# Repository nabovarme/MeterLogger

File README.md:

# MeterLogger

MeterLogger is a custom daughterboard you can insert in Kamstrup Meters and get them to transmit their samples 
to a remote MQTT server.
MeterLogger is part of the [**Nabovarme**](https://github.com/nabovarme) organization.

Check out the [WIKI](https://github.com/nabovarme/MeterLogger/wiki) for more details!

## 🚀 Modern GUI-Based Flashing & Rebuilding

You no longer need local compilers, toolchains, or command-line flash utilities on your host machine. Building and flashing are now fully virtualized via Docker and executed directly from your web browser.

### How to Flash:
1. Navigate to the **Firmware Flash Tool** tab on your MeterLoggerWeb dashboard
2. Connect your ESP8266/MeterLogger board via USB.
3. Select your desired firmware profile from the search bar (tied directly to your meter serial).
4. Click **Flash Device**. Your browser will request access to the USB serial port via the **WebSerial API** and write the firmware directly at up to 1.5 Mbps.

### How to Rebuild Custom Firmware:
If you need custom parameters (e.g., turning an EN61107 meter into an Impulse meter or disabling Auto-Close):
1. Expand the **Custom Firmware Build Settings** panel.
2. Select your targets (e.g., Protocol, Valve overrides, debug flags).
3. Click **Rebuild Firmware**.
4. This dispatches an asynchronous build task to the Dockerized `firmware_builder` service on your host. Once compiled (usually < 30 seconds), the new image is indexed and immediately ready to be flashed in the selector above.

## Build details (old procedure)

To build and flash for KMP type meter (Multical 601):  
```
KEY=ef500c9268cf749016d26d6cbfaaf7bf make clean all flashall
```
 
To build and flash for EN61107, sub type Multical 66 C:  
```
EN61107=1 KEY=ef500c9268cf749016d26d6cbfaaf7bf make clean all flashall
```
 
To build and flash for EN61107, sub type Multical 66 B:  
```
MC_66B=1 KEY=ef500c9268cf749016d26d6cbfaaf7bf make clean all flashall
```
 
To build and flash for KMP/EN61107 type, forced as flow meter:  
```
FLOW_METER=1 KEY=ef500c9268cf749016d26d6cbfaaf7bf make clean all flashall
```
 
To build and flash for impulse-based electricity meter:  
```
IMPULSE=1 KEY=ef500c9268cf749016d26d6cbfaaf7bf make clean all flashall
```
 
To configure wireless network:  
```
SERIAL=9999999 KEY=ef500c9268cf749016d26d6cbfaaf7bf make wifisetup
```
 
**BUILD OPTIONS**  

DEBUG=1  
enable serial debugging  

DEBUG_NO_METER=1  
don't wait for meter to answer serial. Build for nodemcu board  

IMPULSE_DEV_BOARD=1  
build for nodemcu board  

DEBUG_SHORT_WEB_CONFIG_TIME=1  
don't wait for web config  

IMPULSE=1  
meter type is impulse-based (100 mS)  

EN61107=0  
meter type is KMP (Multical 601)  

EN61107=1  
meter type is EN61107, sub type Multical 66 C  

MC_66B=1  
meter type is EN61107, sub type Multical 66 B  

FLOW_METER=1  
meter is forced to run as a flow meter and close when volume is reached  

AUTO_CLOSE=1  
automatically check if energy is larger than the value set by open_until MQTT command  

DEBUG_STACK_TRACE=1  
Enable exception stack trace dump to flash at address STACK_TRACE_SEC * SPI_FLASH_SEC_SIZE (0x80000), STACK_TRACE_N bytes  

DISABLE_LED=1  
completely disable LED blinking routines and hardware setup while keeping API stub functions intact  

NO_CRON=1  
disable cron stuff and save 2688 bytes of RAM. Reconfiguration is needed after changing this  

THERMO_NO=0  
thermo actuator is normally closed  

THERMO_NO=1  
thermo actuator is normally open  

THERMO_ON_AC_2  
thermo actuator connected on AC 2  

LED_ON_AC=1  
use LED to indicate AC state  

AC_TEST=1  
run a test pattern on AC out and blink LED  

SERIAL=9999999  
serial number for meter used for device's SSID: IMPULSE meters EL_9999999 and other Kamstrup meters KAM_9999999. Used in make wifisetup target and if DEBUG_NO_METER=1  

KEY=ef500c9268cf749016d26d6cbfaaf7bf  
master key for crypto, 16 bytes  
First 8 bytes hex encoded (ef500c9268cf7490) is Wi-Fi setup password. Master key is SHA256 hashed to 32 bytes and first 16 bytes is AES key and last 16 bytes is HMAC SHA256 key.

```
master key                            wifi key (first 16 bytes)
+--------------------------------+    +----------------+
|ef500c9268cf749016d26d6cbfaaf7bf| -> |ef500c9268cf7490| 
+--------------------------------+    +----------------+
                |
          [sha256 hash]
                |
                v
+----------------------------------------------------------------+
|89a5d4f82ad86bc9ec27427e246fd15481663afea8c463d93cc93c967c9b31be|
+----------------------------------------------------------------+
                |                                        |
aes key         v                   hmac sha256 key      v
+--------------------------------+  +--------------------------------+
|89a5d4f82ad86bc9ec27427e246fd154|  |81663afea8c463d93cc93c967c9b31be|
+--------------------------------+  +--------------------------------+

```

Crypto is applied on MQTT packages like this:
1) at 32 bytes offset in mqtt_message contains IV, 16 bytes random bytes used for AES128 CBC encryption.

2) cleartext (0-terminated) is AES128 CBC encrypted, with AES key and IV. Result is written to mqtt_message at 32 + 16 bytes offset (binary data not 0-terminated).

3) HMAC SHA256 checksum is calculated on topic + IV + encrypted data and written to first 32 bytes.

```
hmac sha256                                                       IV                               encrypted data
+----------------------------------------------------------------+--------------------------------+------------------------------------+
|b218d7ec2f7977c942b5bf16d535de3cb5f0e012638148e5a7fc6e09efe440a7|54cd3d04f024e7e5c4876248cc146c41|9616bb291182861b7a5ea238a0c267115...|
+--------------------------------------------------------------------------------------------------------------------------------------+

IV
+--------------------------------+
|54cd3d04f024e7e5c4876248cc146c41| 
+--------------------------------+

cleartext message (null terminated)
+-----------------------------------------------------------------------------------------------------------------+
|heap=21376&t1=23.61 C&t2=22.19 C&tdif=1.42 K&flow1=0 l/h&effect1=0.0 kW&hr=73327 h&v1=1321.27 m3&e1=56.726 MWh&\0|
+-----------------------------------------------------------------------------------------------------------------+

+

hmac sha256 key
```

## Flash Memory Map (1MB ESP07)

The firmware relies on a strict dual-ROM partition layout to support rBoot Over-The-Air (OTA) updates and a dedicated LittleFS/ESPFS webserver filesystem. It is critical that configuration blocks and crash logs do not overlap with executable ROM spaces.

| Start Address | End Address | Size (KB) | Purpose |
| :--- | :--- | :--- | :--- |
| `0x00000` | `0x00FFF` | 4 KB | **rBoot Bootloader** (`rboot.bin`) |
| `0x01000` | `0x01FFF` | 4 KB | **rBoot Configuration** (`blank.bin`) |
| `0x02000` | `0x75FFF` | 464 KB | **ROM 0** (`user1.bin` / Primary Firmware Slot) |
| `0x76000` | `0x7BFFF` | 24 KB | **System Configuration** (`CFG_LOCATION` / Wi-Fi credentials & states) |
| `0x7C000` | `0x81FFF` | 24 KB | **Web UI Filesystem** (`webpages.espfs` / HTML/CSS/JS assets) |
| `0x82000` | `0xF7FFF` | 472 KB | **ROM 1** (`user2.bin` / Secondary OTA Firmware Slot) |
| `0xF8000` | `0xFBFFF` | 16 KB | **Stack Trace Crash Log** (`STACK_TRACE_SEC` / Exception Handler dumps) |
| `0xFC000` | `0xFDFFF` | 8 KB | **ESP8266 System Init Data** (`esp_init_data_default_112th_byte_0x03.bin`) |
| `0xFE000` | `0xFFFFF` | 8 KB | **System Blank** (`blank.bin`) |

*Note: The `STACK_TRACE_SEC` must be strictly set to `0xF8` in `user_config.h` to prevent the crash logger from corrupting ROM 1 or the web filesystem during exception handling.*

**MQTT format for messages sent _to_ meter**  

| Topic                                               | Message                                                                                                                                            |
| :-------------------------------------------------- | :------------------------------------------------------------------------------------------------------------------------------------------------- |
| /config/v2/9999999/[unix time]/open_until           | [kWh when meter should close (only write to flash if changed and not negative value)]                                                              |
| /config/v2/9999999/[unix time]/open_until_delta     | [[kWh when meter should close as delta (only write to flash if changed and not negative value)]                                                    |
| /config/v2/9999999/[unix time]/set_cron             | minute=30&hour=*&day_of_month=*&month=*&day_of_week=*&command=[open\|close\|set_ssid_pwd...\|clear_cron]                                           |
| /config/v2/9999999/[unix time]/read_stack_trace     | [offset=0] Requests a chunk of the saved exception handler crash log.                                                                              |
| /config/v2/9999999/[unix time]/set_ssid             | [ssid]                                                                                                                                             |
| /config/v2/9999999/[unix time]/set_pwd              | [pwd]                                                                                                                                              |
| /config/v2/9999999/[unix time]/set_ssid_pwd         | [ssid=name&pwd=secret]                                                                                                                             |
| /config/v2/9999999/[unix time]/test_ssid_pwd        | [ssid=name&pwd=secret&stay=seconds]                                                                                                                |
| /config/v2/9999999/[unix time]/set_ap_mesh_pwd      | [pwd]                                                                                                                                              |
| /config/v2/9999999/[unix time]/start_fallback_ap    | [seconds] temporarily broadcasts the fallback rescue network (no flash write)                                                                      |
| /config/v2/9999999/[unix time]/ota_update           | [url=http://domain.com/api&version=20261013_001000&sha256_user1=<64-char_hex_hash>&sha256_user2=<64-char_hex_hash>] (all optional; meter selects correct hash based on target slot) OR [action=confirm] (permanently commits) |
| /config/v2/9999999/[unix time]/set_key              | [key=new_32_char_hex_key]                                                                                                                          |
| /config/v2/9999999/[unix time]/set_mqtt_host        | [MQTT hostname, e.g. nabovarme.meterlogger.net; saved to flash and device restarts after replying]                                                 |
| &nbsp;                                              | &nbsp;                                                                                                                                             |
| /config/v2/9999999/[unix time]/ping                 |                                                                                                                                                    |
| /config/v2/9999999/[unix time]/open                 |                                                                                                                                                    |
| /config/v2/9999999/[unix time]/close                |                                                                                                                                                    |
| /config/v2/9999999/[unix time]/status               |                                                                                                                                                    |
| /config/v2/9999999/[unix time]/cron                 |                                                                                                                                                    |
| /config/v2/9999999/[unix time]/clear_cron           |                                                                                                                                                    |
| /config/v2/9999999/[unix time]/version              |                                                                                                                                                    |
| /config/v2/9999999/[unix time]/uptime               |                                                                                                                                                    |
| /config/v2/9999999/[unix time]/vdd                  |                                                                                                                                                    |
| /config/v2/9999999/[unix time]/rssi                 |                                                                                                                                                    |
| /config/v2/9999999/[unix time]/ssid                 |                                                                                                                                                    |
| /config/v2/9999999/[unix time]/scan                 |                                                                                                                                                    |
| /config/v2/9999999/[unix time]/wifi_status          |                                                                                                                                                    |
| /config/v2/9999999/[unix time]/start_ap             |                                                                                                                                                    |
| /config/v2/9999999/[unix time]/stop_ap              |                                                                                                                                                    |
| /config/v2/9999999/[unix time]/fallback_status      |                                                                                                                                                    |
| /config/v2/9999999/[unix time]/ap_status            |                                                                                                                                                    |
| /config/v2/9999999/[unix time]/reconnect            |                                                                                                                                                    |
| /config/v2/9999999/[unix time]/disconnect_count     |                                                                                                                                                    |
| /config/v2/9999999/[unix time]/network_quality      |                                                                                                                                                    |
| /config/v2/9999999/[unix time]/mem                  |                                                                                                                                                    |
| /config/v2/9999999/[unix time]/chip_id              |                                                                                                                                                    |
| /config/v2/9999999/[unix time]/flash_id             |                                                                                                                                                    |
| /config/v2/9999999/[unix time]/flash_size           |                                                                                                                                                    |
| /config/v2/9999999/[unix time]/crypto               |                                                                                                                                                    |
| /config/v2/9999999/[unix time]/reset_reason         |                                                                                                                                                    |
| /config/v2/9999999/[unix time]/restart              |                                                                                                                                                    |

**MQTT format for messages sent _from_ meter**  

| Topic | Message |
| :--- | :--- |
| /sample/v2/9999999/[unix time]                      | heap=20000&t1=25.00 C&t2=15.00 C&tdif=10.00 K&flow1=0 l/h&effect1=0.0 kW&hr=0 h&v1=0.00 m3&e1=0 kWh&                                               |
| /cron/v2/9999999/[unix time]                        | [number of active cron jobs]                                                                                                                       |
| /ping/v2/9999999/[unix time]                        |                                                                                                                                                    |
| /version/v2/9999999/[unix time]                     | [sdk version]-[git version]-[lwip version]-[hardware model]                                                                                        |
| /status/v2/9999999/[unix time]                      | [open\|close]                                                                                                                                      |
| /open_until/v2/9999999/[unix time]                  | [kWh when meter should close]                                                                                                                      |
| /open_until_delta/v2/9999999/[unix time]            | [kWh when meter should close]                                                                                                                      |
| /uptime/v2/9999999/[unix time]                      | [uptime in seconds]                                                                                                                                |
| /stack_trace_result/v2/9999999/[unix time]          | [offset=0&data=Stack%20dump%3A%0A...] URL-escaped block of the recorded stack trace. Returns empty data if end of log is reached.                  |
| /vdd/v2/9999999/[unix time]                         | [power supply voltage level]                                                                                                                       |
| /rssi/v2/9999999/[unix time]                        | [rssi of the wifi it is connected to (in dBm, 31 if fail)]                                                                                         |
| /ssid/v2/9999999/[unix time]                        | [ssid of the wifi it is connected to]                                                                                                              |
| /set_ssid/v2/9999999/[unix time]                    | [ssid of the wifi it is set to connect to]                                                                                                         |
| /set_pwd/v2/9999999/[unix time]                     | [password for the wifi it is set to connect to]                                                                                                    |
| /set_ssid_pwd/v2/9999999/[unix time]                | ssid=[name]&pwd=[secret]                                                                                                                           |
| /test_ssid_pwd/v2/9999999/[unix time]               | ssid=[name]&pwd=[secret]&stay=[seconds]                                                                                                            |
| /test_ssid_pwd_result/v2/9999999/[unix time]        | [status=ok&ssid=the_ssid&rssi=-62&reason=none&time_ms=3100] (or status=failed&ssid=the_ssid&rssi=0&reason=4way_handshake_timeout&time_ms=15000)    |
| /set_ap_mesh_pwd/v2/9999999/[unix time]             | [password for the mesh-[serial] itself]                                                                                                            |
| /scan/v2/9999999/[unix time]                        | [empty reply to acknowledge scan command]                                                                                                          |
| /scan_result/v2/9999999/[unix time]                 | [ssid=Loppen Public&bssid=xx:xx:xx:xx:xx:xx&rssi=-51&channel=11&auth_mode=...&pairwise_cipher=...&group_cipher=...&phy_11b=...&phy_11g=...&phy_11n=...&wps=...] |
| /start_fallback_ap/v2/9999999/[unix time]           | [seconds] immediate parameter echo                                                                                                                 |
| /fallback_status/v2/9999999/[unix time]             | [active\|inactive]                                                                                                                                 |
| /wifi_status/v2/9999999/[unix time]                 | [connected|<disconnect_reason_string>] (e.g., connected, no_ap_found, auth_expire)                                                                 |
| /ap_status/v2/9999999/[unix time]                   | [started\|stopped]                                                                                                                                 |
| /disconnect_count/v2/9999999/[unix time]            | [number of disconnects]                                                                                                                            |
| /network_quality/v2/9999999/[unix time]             | ping_response_time=[2.000 mS\|unknown]&ping_average_packet_loss=[0.00%\|unknown]&disconnect_count=[0]                                              |
| /cnx_csa_fn_called/v2/9999999/[unix time]           | count=[number of intercepted CSA calls]                                                                                                            |
| /flash_error/v2/9999999/[unix time]                 | calculated_crc=[0x...]&saved_crc=[0x...]                                                                                                           |
| /mem/v2/9999999/[unix time]                         | heap=9672                                                                                                                                          |
| /flash_id/v2/9999999/[unix time]                    | 0x164020                                                                                                                                           |
| /flash_size/v2/9999999/[unix time]                  | 4096 kB                                                                                                                                            |
| /reset_reason/v2/9999999/[unix time]                | reason=[int]&exccause=[int]&epc1=[0x...]&epc2=[0x...]&epc3=[0x...]&excvaddr=[0x...]&depc=[0x...]                                                   |
| /restart/v2/9999999/[unix time]                     |                                                                                                                                                    |
| /ota_update/v2/9999999/[unix time]                  | [status=started&target_rom=1\|2] (Progress: status=flashing_10%..90%. Success: status=success&target_rom=1\|2, status=restarting_in_22s, status=self_test_passed_committed, status=already_committed. Errors: status=error\_...) |
| /set_key/v2/9999999/[unix time]                     | [status=ok (or status=error_invalid_key)]                                                                                                          |
| /set_mqtt_host/v2/9999999/[unix time]               | [status=ok (or status=error_invalid_host)]                                                                                                         |

**Secure OTA Updates with Dual SHA-256 Validation:**  
The OTA (Over-The-Air) firmware update process now features streaming cryptographic verification to prevent corrupted downloads from soft-bricking the device. Because the ESP8266 rBoot bootloader requires two separate memory slots, user1.bin and user2.bin are compiled with different memory layouts and consequently have completely different SHA-256 hashes.

To ensure safety without requiring the server to track which slot the meter is currently using, the MQTT RPC payload accepts both hashes (sha256_user1 and sha256_user2). As the meter streams the HTTP download into flash, it calculates the SHA-256 hash on the fly. Before switching the boot slot, it verifies the downloaded file against both provided hashes. If the checksum does not match, the update is aborted, an error is reported over MQTT, and the device safely reboots into the existing valid firmware.

**Note on Wi-Fi Test Reason Codes:**  
The `reason` field in the `/test_ssid_pwd_result` payload maps to ESP8266 SDK disconnect codes. The most common are:
* **none**: Success (No error)
* **4way_handshake_timeout**: Wrong Password 
* **no_ap_found**: Network Not Found / Out of Range
* **auth_expire**: AP Rejected Authentication 
* **timeout**: Custom code for internal timeout (Test took longer than 15 seconds)

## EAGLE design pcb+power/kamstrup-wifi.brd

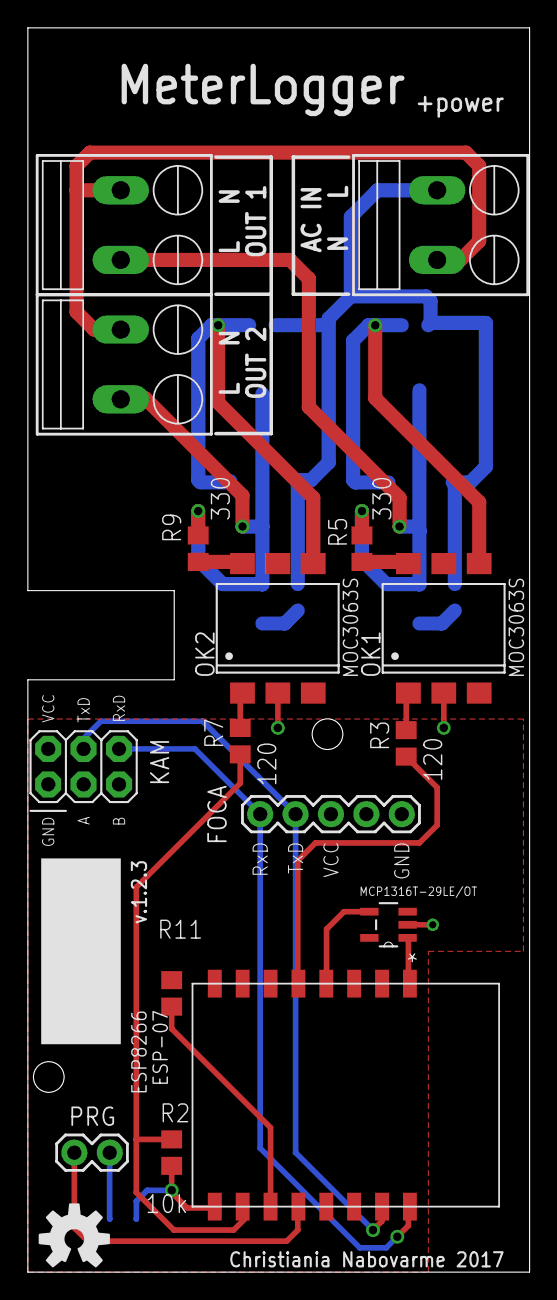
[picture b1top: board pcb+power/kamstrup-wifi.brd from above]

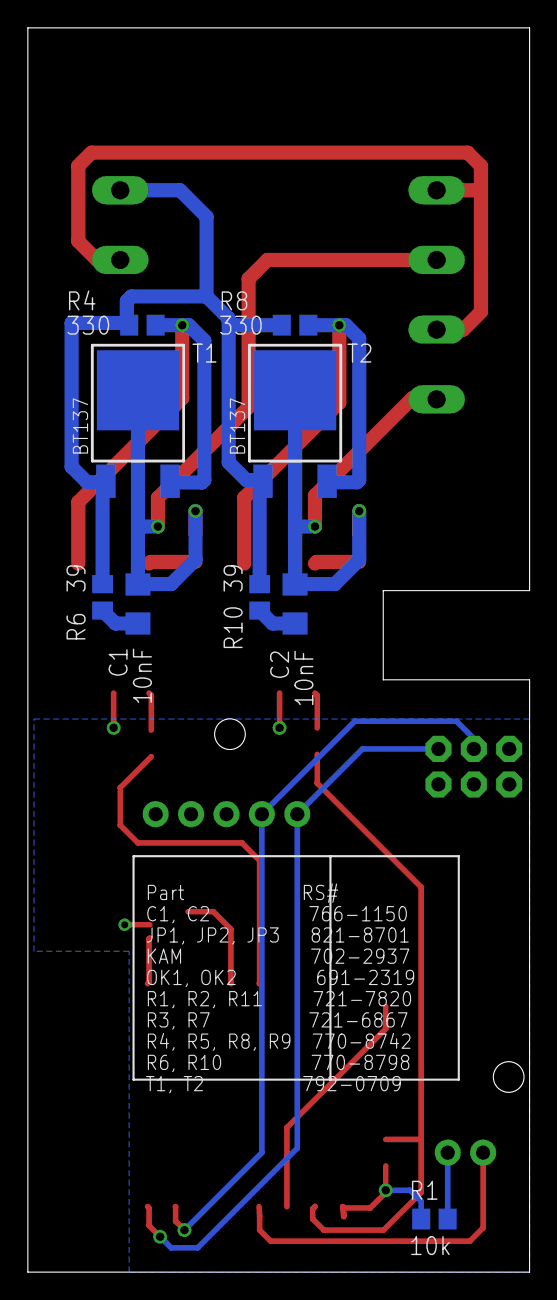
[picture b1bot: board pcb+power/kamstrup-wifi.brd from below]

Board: 2 copper layers, 36.0 x 89.3 mm, 26 parts (9 on the bottom side), 23 nets.

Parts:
C1, C2: 10nF; C1206
FOCA: 1X05
JP1: AC IN; SCREWTERMINAL-5MM-2
JP2: AC OUT 1; SCREWTERMINAL-5MM-2
JP3: AC OUT 2; SCREWTERMINAL-5MM-2
KAM: 2X03
OK1, OK2: MOC3063S; DIL6-SMD
PRG: M02PTH; 1X02
R1, R2, R11: 10k; R0805
R3, R7: 120; R0805
R4, R5, R8, R9: 330; R0805
R6, R10: 39; R0805
T1, T2: BT137; SOT428
U1: ESP8266-07; ESP-07
U2: MCP1316T-29LE/OT; SOT95P270X145-5N
U$2: OSHW-LOGO-M

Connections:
3.3V: FOCA.3, KAM.2, R11.1, U1.CH_PD, U1.VCC, U2.5
GND: FOCA.5, KAM.1, OK1.2, OK2.2, R1.1, R2.1, U1.GND, U2.2
unnamed: FOCA.1, KAM.6, U1.TXD
unnamed: FOCA.2, KAM.4, U1.RXD
unnamed: PRG.2, U1.GPIO0
unnamed: PRG.1, R1.2
unnamed: OK2.1, R7.2
unnamed: OK2.4, R8.1, T2.3
unnamed: OK2.6, R9.1
unnamed: C2.1, JP3.2, R9.2, T2.4
unnamed: JP1.1, R4.2, R6.1, R8.2, R10.1, T1.1, T2.1
unnamed: C2.2, R10.2
unnamed: R3.1, U1.GPIO14
unnamed: OK1.1, R3.2
unnamed: OK1.4, R4.1, T1.3
unnamed: OK1.6, R5.1
unnamed: C1.1, JP2.2, R5.2, T1.4
unnamed: R2.2, R7.1, U1.GPIO15
unnamed: C1.2, R6.2
unnamed: JP1.2, JP2.1, JP3.1
unnamed: U1.REST, U2.1
unnamed: U1.GPIO16, U2.4
unnamed: R11.2, U1.GPIO2

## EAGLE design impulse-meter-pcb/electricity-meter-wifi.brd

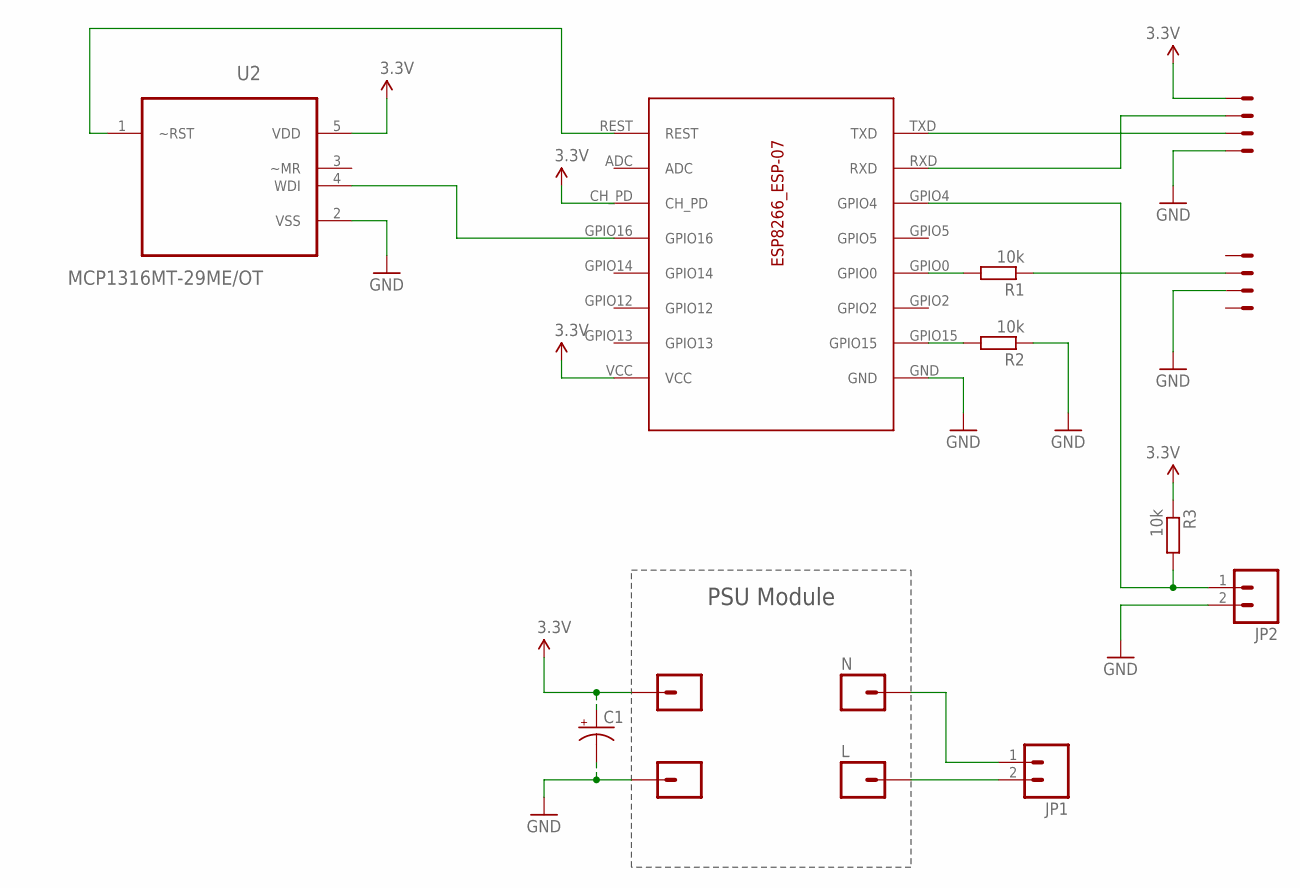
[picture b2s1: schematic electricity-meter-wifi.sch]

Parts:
3.3V: M01PTH_2MM; 1X01_2MM
C1: CAP_POLD; PANASONIC_D
ESP8266_ESP-07: ESP8266-07; ESP-07
GND: M01PTH_2MM; 1X01_2MM
JP1, JP2: M02PTH3_5MM; 1X02_LONGPADS
L: M01PTH_2MM; 1X01_2MM
N: M01PTH_2MM; 1X01_2MM
R1, R2, R3: 10k; R0805
U2: MCP1316MT-29ME/OT; SOT95P270X145-5N
U$1: CON-PCB-SLOT-0.05MINIMAL; CONN_SLOT_MINIMAL

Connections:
3.3V: 3.3V.1, C1.+, ESP8266_ESP-07.CH_PD, ESP8266_ESP-07.VCC, R3.1, U2.5 (VDD), U$1.4; also elsewhere on the board
GND: C1.-, ESP8266_ESP-07.GND, GND.1, JP2.2, R2.1, U2.2 (VSS), U$1.1, U$1.7; also elsewhere on the board
unnamed: ESP8266_ESP-07.TXD, U$1.2
unnamed: ESP8266_ESP-07.RXD, U$1.3
unnamed: ESP8266_ESP-07.GPIO4, JP2.1, R3.2
unnamed: ESP8266_ESP-07.GPIO0, R1.2
unnamed: JP1.2, L.1
unnamed: JP1.1, N.1
unnamed 8: ESP8266_ESP-07.GPIO15, R2.2; also elsewhere on the board
unnamed: ESP8266_ESP-07.REST, U2.1 (~RST)
unnamed: ESP8266_ESP-07.GPIO16, U2.4 (WDI)
unnamed 11: ESP8266_ESP-07.GPIO12; also elsewhere on the board
unnamed: R1.1, U$1.6
unnamed 13: ESP8266_ESP-07.GPIO13; also elsewhere on the board
unnamed 14: ESP8266_ESP-07.GPIO14; also elsewhere on the board
unnamed 15: ESP8266_ESP-07.GPIO2; also elsewhere on the board

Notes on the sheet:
PSU Module

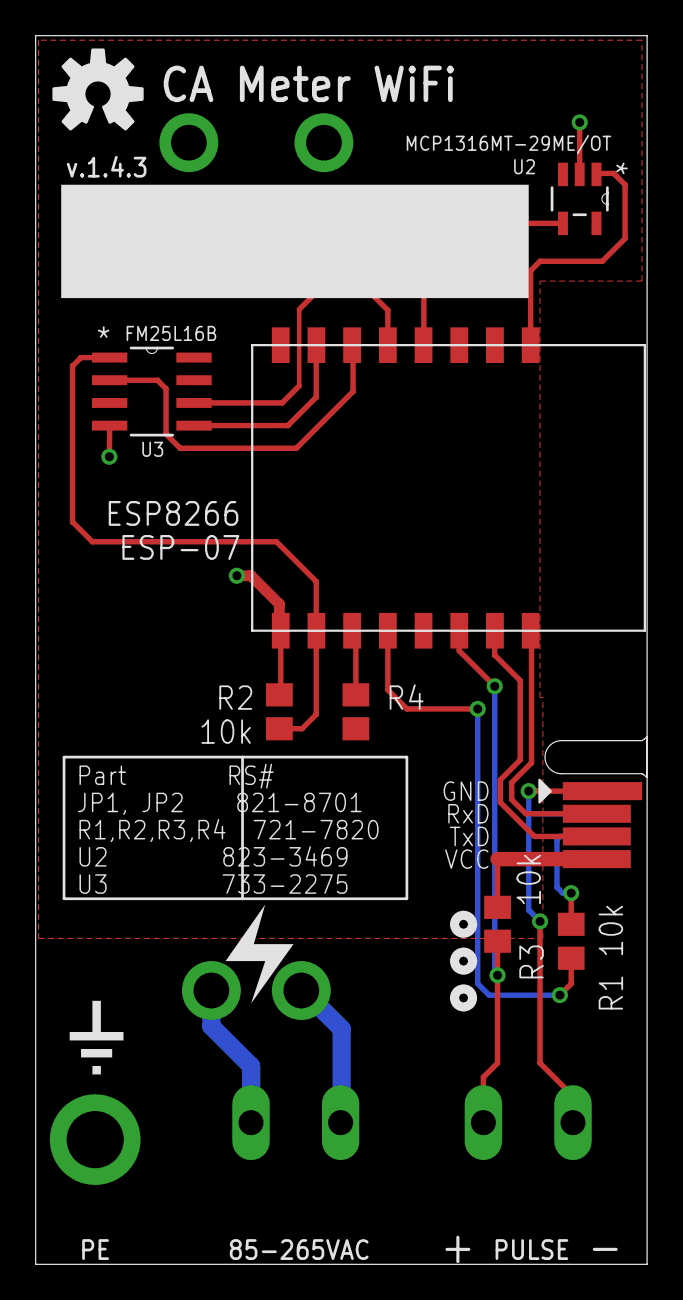
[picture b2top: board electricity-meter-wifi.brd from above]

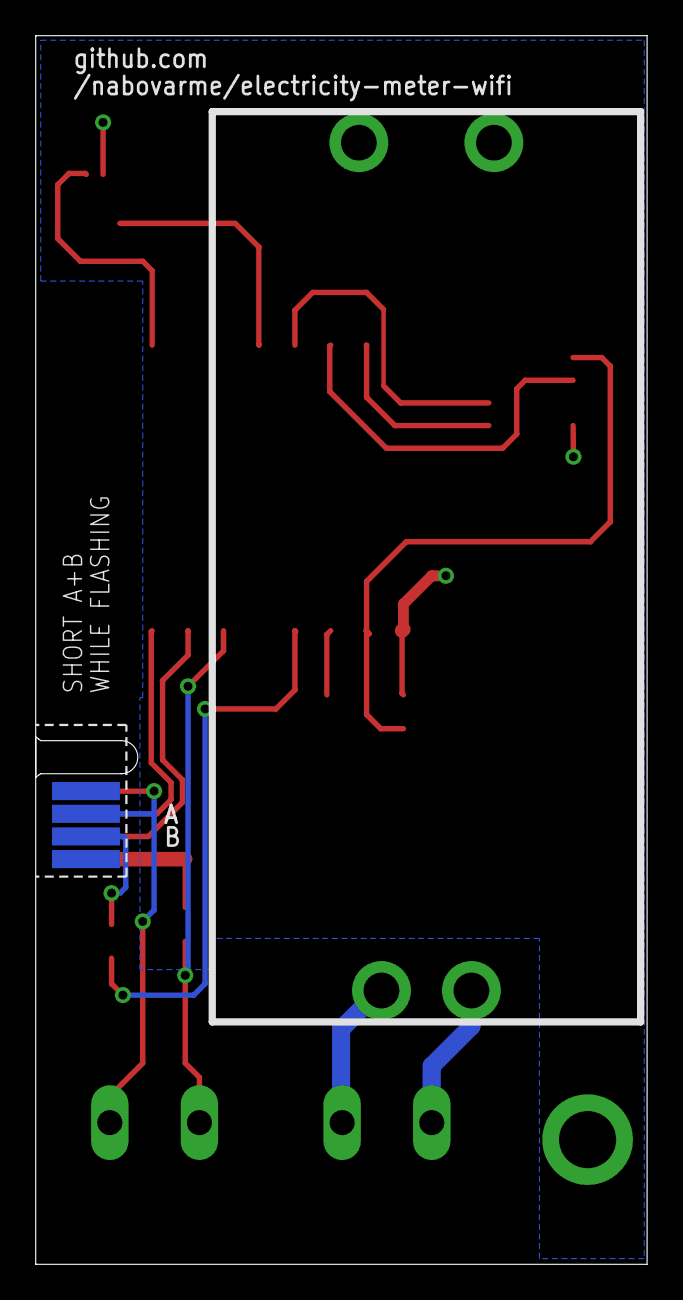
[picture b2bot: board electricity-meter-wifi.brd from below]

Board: 2 copper layers, 34.3 x 68.8 mm, 15 parts (4 on the bottom side), 16 nets.

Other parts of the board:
R4: 10k; R0805
U3: FM25L16B; SOIC127P600X175-8N
U$2: OSHW-LOGO-M

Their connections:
3.3V: R4.1, U3.3, U3.7, U3.8; also elsewhere on the board
GND: U3.4; also elsewhere on the board
unnamed 8: U3.1; also elsewhere on the board
unnamed 11: U3.2; also elsewhere on the board
unnamed 13: U3.5; also elsewhere on the board
unnamed 14: U3.6; also elsewhere on the board
unnamed 15: R4.2; also elsewhere on the board

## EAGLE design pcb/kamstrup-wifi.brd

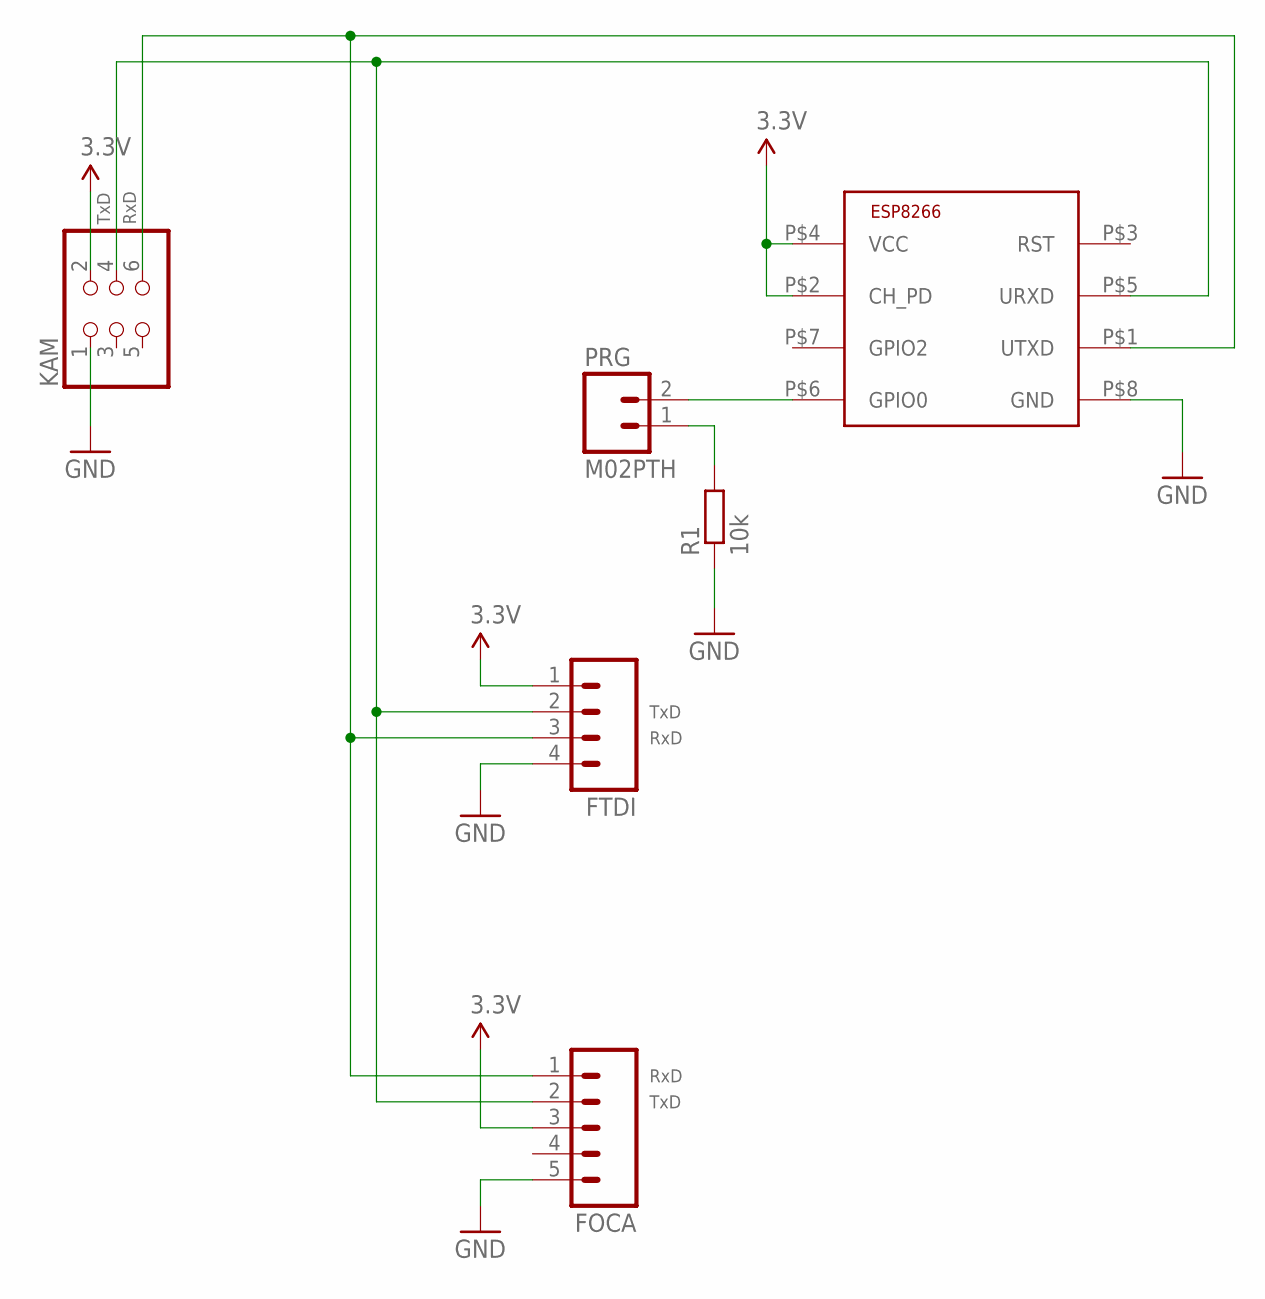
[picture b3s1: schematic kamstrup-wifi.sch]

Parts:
FOCA: M05PTH; 1X05
FTDI: M04PTH; 1X04
KAM: PINHD-2X3; 2X03
PRG: M02PTH; 1X02
R1: 10k; M0805
U$1: ESP8266-01; ESP-01

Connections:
3.3V: FOCA.3, FTDI.1, KAM.2, U$1.P$2 (CH_PD), U$1.P$4 (VCC)
GND: FOCA.5, FTDI.4, KAM.1, R1.1, U$1.P$8 (GND)
unnamed: FOCA.1, FTDI.3, KAM.6, U$1.P$1 (UTXD)
unnamed: FOCA.2, FTDI.2, KAM.4, U$1.P$5 (URXD)
unnamed: PRG.2, U$1.P$6 (GPIO0)
unnamed: PRG.1, R1.2

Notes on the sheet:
RxD
TxD

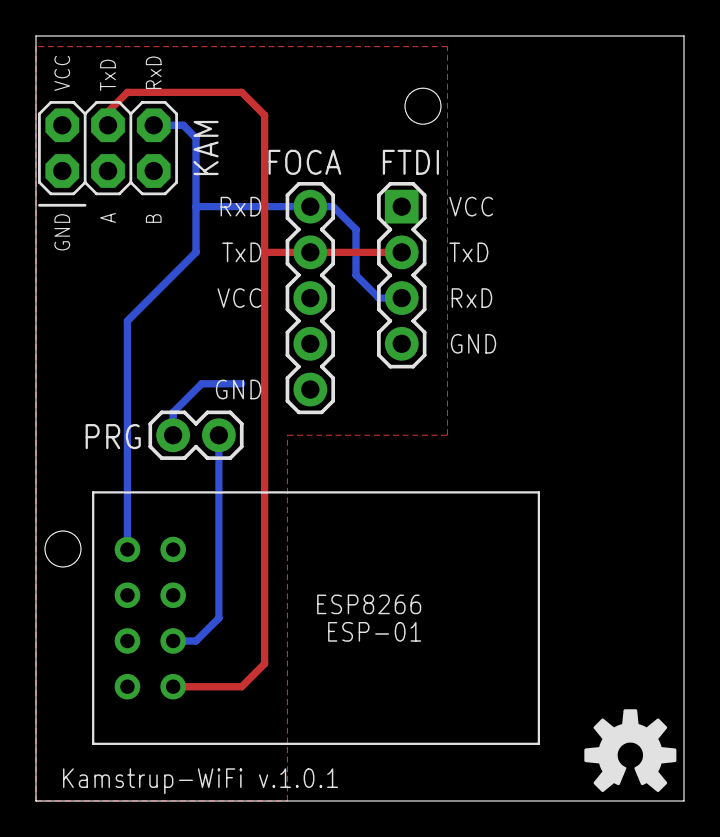
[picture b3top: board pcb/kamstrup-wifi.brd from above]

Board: 2 copper layers, 36.0 x 42.5 mm, 7 parts (1 on the bottom side), 6 nets.

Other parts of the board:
U$2: OSHW-LOGO-M

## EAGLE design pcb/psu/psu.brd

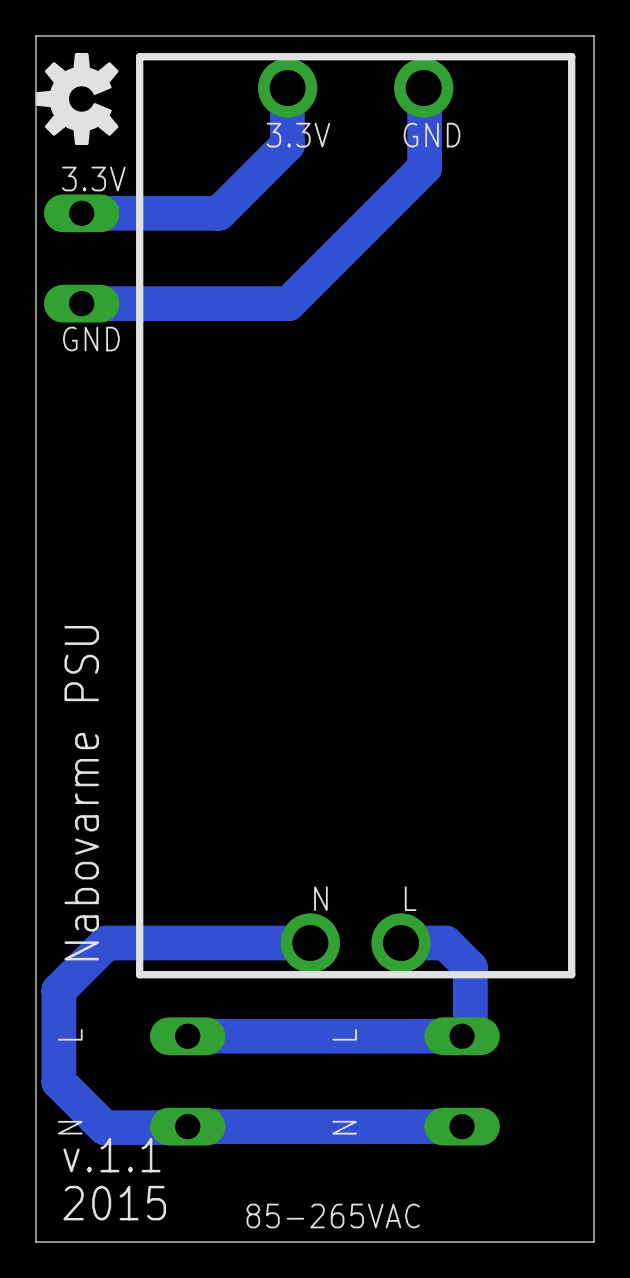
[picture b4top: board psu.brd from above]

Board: 2 copper layers, 31.0 x 67.0 mm, 8 parts (0 on the bottom side), 4 nets.

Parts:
3.3V: M01PTH_2MM; 1X01_2MM
85-265VAC, 85-265VAC1: 1X02_LONGPADS
GND: M01PTH_2MM; 1X01_2MM
JP2: 1X02_LONGPADS
L: M01PTH_2MM; 1X01_2MM
N: M01PTH_2MM; 1X01_2MM
U$1: OSHW-LOGO-M

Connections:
unnamed: 85-265VAC.1, 85-265VAC1.1, L.1
unnamed: 85-265VAC.2, 85-265VAC1.2, N.1
unnamed: 3.3V.1, JP2.1
unnamed: GND.1, JP2.2

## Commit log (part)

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2025-08-01 UNTESTED: Fix cnx_csa_fn_wrapper to use correct variable names for clarity
    - Renamed `next_instr` to `continue_addr` for consistency and clarity
    - Fixed incorrect variable name `literal_addr` to `literal_a13` in inline assembly
    - Ensures a13 is correctly restored using the intended literal address
2025-08-01 Fix patch bytes in Makefile for cnx_csa_fn wrapper jump
    - Updated PATCH_PREFIX in patch rule to include correct l32r and jx instructions with proper padding
    - Adjusted PATCH_BYTES concatenation to match new PATCH_PREFIX and wrapper address layout
    - Ensures correct instruction encoding and alignment for patched cnx_csa_fn function entry
2025-08-01 STILL REBOOTS. Fix cnx_csa_fn patch prefix and implement wrapper to resume original function
    - Corrected PATCH_PREFIX in Makefile to properly assemble the patched instruction
    sequence (`f03d` moved from 3rd to 2nd instruction slot).
    - Added cnx_csa_fn_wrapper() to replace the original cnx_csa_fn, checking Wi-Fi
    status and conditionally returning early if not connected.
    - Wrapper replicates the original `l32r a13, 0x40210000` behavior, then resumes
    execution at 0x4021783c to continue the original function logic.
2025-08-01 fix: replay overwritten instructions in cnx_csa_fn_wrapper (still crashes)
    - Updated patch bytes in Makefile to include full original instruction sequence and correct patch prefix
    - Changed cnx_csa_fn_wrapper to replay all overwritten instructions including:
    * saving registers (a13, a12, a14, a0) to stack
    * restoring a13 literal via l32r
    * performing addmi instruction to correctly adjust a12
    * jumping to the original code flow after replaying instructions
2025-08-02 Use local linker script if available; add patch literal reference
2025-08-02 fix: place cnx_csa_fn_wrapper_literal close to cnx_csa_fn via linker script
    - Introduce dedicated linker section `.cnx_csa_fn_wrapper.literal` for
    `cnx_csa_fn_wrapper_literal` to ensure it is located physically close to
    `cnx_csa_fn`.
    - Update linker script to place this section near the `libnet80211.a` text
    and literal sections containing `cnx_csa_fn`.
    - Adjust `cnx_csa_fn_wrapper_literal` declaration in wifi.c to use this
2025-08-02 build: include patch target in default build and fix wrapper patch details
    - Add 'patch' as a dependency of 'all' target in Makefile to ensure patching happens automatically.
    - Correct cnx_csa_fn_wrapper resume address and literal pointer in wifi.c for accurate control flow.
    - Remove unnecessary register saves and instructions from wrapper for cleaner code.
    - Update patch_cnx_fn.sh patch length comment to reflect correct 8-byte patch size.
    - Update wrapper to properly re-execute overwritten instructions by jumping to the correct continuation address after patch.
2025-08-02 build: update patch target to include version string modification
    - After applying patch_cnx_fn.sh, also patch firmware version string by replacing
    "-dev" with "+dev" directly in the binary.
    - Ensures version clearly reflects patched firmware state.
2025-08-02 wifi: clean up debug layout and make cnx_csa_fn_wrapper debug-safe
    - Moved `cnx_csa_fn_wrapper()` declaration outside of `#ifdef DEBUG`
    to ensure it’s always linked and available.
    - Refactored internal timer function declarations for consistency.
    - Avoided use of os_printf() directly within cnx_csa_fn_wrapper(),
    replacing it with a debug flag (`debug_print_cnx_csa_fn`) and timer
    to safely log wrapper entry from task context.
2025-08-02 ld: ensure cnx_csa_fn_wrapper literal section is retained in final binary
    Wrap .cnx_csa_fn_wrapper.literal section in KEEP() to prevent the linker from
    discarding it during optimization. This ensures that the literal holding the
    wrapper address is preserved and placed near cnx_csa_fn in flash.
    This is critical for correct l32r instruction behavior, which relies on the
    literal being within reachable offset range.
2025-08-02 Declare debug_print_cnx_csa_fn as volatile
2025-08-03 patch_cnx_fn.sh: pad patch with NOPs to match original instruction length
    patch_cnx_fn.sh: pad patch with NOPs to match original instruction length
    40217834 <cnx_csa_fn>:
    40217834: e1f321 l32r a2, 40210000 <cnx_csa_fn_wrapper_literal>
    40217837: 0002a0 jx a2
    4021783a: f03d nop.n
    4021783c: f03d nop.n
2025-08-03 Simplify debug print for cnx_csa_fn_wrapper_literal
    Change debug_print_patch() to print cnx_csa_fn_wrapper_literal directly,
    removing unnecessary pointer casting and dereferencing for clarity.
2025-12-18 fix: properly switch AP mode before updating SSID/password
    Temporarily disables the AP if enabled before calling
    wifi_softap_set_config to avoid blank SSID issues. Restores
    the original Wi-Fi mode afterward. Also sets ssid_len to the
    actual SSID length instead of 0 to prevent empty SSID.
2026-01-11 fix(kmp): replace naive int power function with exponentiation by squaring
    - Original `kmp_pow(int a, int b)` used a linear loop with off-by-one bug for b=0.
    - New implementation uses exponentiation by squaring (O(log b)), producing the same results for all b>0 and correctly returns 1 for b=0.
    - Improves performance for large exponents and fixes edge case.
2026-01-11 kmp: make kmp_pow if statement multiline and add explanatory comments
2026-01-21 Fix SoftAP SSID being overridden to default ESP-xxxxxx
    - wifi_softap_config() no longer changes Wi-Fi operation mode,
    preventing the SoftAP SSID from reverting to the default ESP name.
    - Keep ssid_len properly set to the length of the configured SSID.
2026-01-21 Fix SSID string comparison to prevent buffer overreads
    - Replaced unsafe strncmp calls using sizeof() with length-checked comparisons
    - Added explicit checks using stationConf.ssid_len and strlen(sys_cfg.sta_ssid)
    - Preserved all existing null checks (info != NULL && info->ssid != NULL)
    - Applies to both default and fallback SSID handling in wifi_handle_event_cb and wifi_scan_done_cb"
2026-01-23 Fix SSID comparison using station_config (remove ssid_len usage)
2026-01-23 fix: use exact SSID match instead of strncmp for Wi-Fi events and scan
    Replace all strncmp() checks on stationConf.ssid and bss_info.ssid
    with memcmp() using the exact length (ssid_len for scanned networks
    and strlen for configured SSID).
    This ensures exact matches, avoids partial/prefix matches, and is
    safe for non-null-terminated SSID buffers in ESP8266 Wi-Fi structures.
2026-02-11 Add MQTT RPC for chip ID
    - Implement `mqtt_rpc_chip_id()` to return the device's chip ID over MQTT.
    - Update `mqtt_data_cb()` to dispatch "chip_id" commands to the new RPC.
    - Update `mqtt_rpc.h` to include the new function declaration.
    - Update README with `/config/v2/.../chip_id` and `/chip_id/v2/...` message format.
2026-02-11 Update comments in mqtt_data_cb for clarity
    - Improved existing comments to better explain the purpose of each block.
    - Clarified buffer handling, decryption, and replay attack checks.
    - Corrected minor typos and inconsistencies in function-specific comments (e.g., "wifi_status", "scan").
    - Retained all original comments and code logic; no functional changes.
2026-02-12 Add chip ID debug print and unify MQTT chip_id topic format
    - Updated mqtt_rpc_chip_id() to use meter-specific serial numbers
    (EN61107, IMPULSE, KMP) for MQTT topic instead of chip ID.
    - Ensured cleartext chip ID is lowercase hex (0x%06x) for consistency.
    - Added chip ID debug print in user_init() for easier device identification.
2026-02-12 Fix flash ID print formatting in user_init()
    - Updated "Flash id" to "Flash ID" for consistent capitalization in debug output.
2026-02-26 Add MQTT RPC command to report active NAT table entries
    - Introduced `mqtt_rpc_nat_table()` to query the current number of
    active NAPT entries via `ip_napt_count()`.
    - Publishes the count over MQTT under `/nat_status/v2/<serial>/<timestamp>`.
    - Added declaration in `mqtt_rpc.h` and integrated handling in
    `user_main.c` for the `"nat_table"` RPC command.
2026-02-26 typo fixed: missing parameter &mqtt_client to mqtt_rpc_nat_table
2026-02-26 Fix NAT table MQTT RPC: use correct variable for debug print
    - Corrected missing semicolon on `u16_t napt_count = ip_napt_count();`.
    - Updated debug print to use `napt_count` instead of calling `ip_napt_count()` again.
    - Removed extraneous `#endif` that was not needed.
2026-02-26 Rename MQTT NAT topic to `/nat_table` for consistency
    - Updated MQTT topic in `mqtt_rpc_nat_table()` from `/nat_status/v2/...` to `/nat_table/v2/...`.
2026-02-26 Refactor Wi-Fi AP setup to use configurable password
    Changed all instances of `wifi_softap_config` to use `sys_cfg.ap_mesh_pwd`
    instead of the fixed `AP_MESH_PASS` macro. This allows the AP mesh password
    to be dynamically configured and saved in flash, improving flexibility
    for deployments where the password needs to be updated without recompiling.
2026-02-26 feat(mqtt): add RPC to update AP mesh password over MQTT
    Introduce new RPC handler `mqtt_rpc_set_ap_mesh_pwd()` allowing the
    AP mesh password to be updated remotely via MQTT.
    - Update `sys_cfg.ap_mesh_pwd` and persist to flash (CRC verified)
    - Restart SoftAP with the new password
    - Return encrypted confirmation (AES/HMAC) over QoS 2
    - Register new `set_ap_mesh_pwd` command in dispatcher
2026-03-28 Fix esptool compatibility and add chip specification for merge_bin
    - Switch to python module invocation of esptool (python3 -m esptool)
    - Add configurable ESPTOOL_CHIP variable (default: esp8266)
    - Pass --chip argument to merge_bin to support esptool v4+
    - Ensure compatibility with newer esptool versions requiring explicit chip selection
2026-03-28 Refactor Makefile: remove copy_release target and streamline build flow
    - Remove copy_release target and its dependencies from build
    - Drop copy_release from 'all' target and merge_bin prerequisites
    - Update merge_bin to no longer depend on copy_release
    - Improve merge_bin log message formatting
    - Clean up outdated comments in Makefile header
2026-03-28 merge_bin: use FW_BASE for firmware binary paths
2026-03-28 Add release target to copy merged firmware with serial-based naming
    Introduce a new Makefile target `release` that copies the merged firmware
    binary into the release directory using the device serial as the filename.
    This simplifies firmware distribution and ensures each build is uniquely
    identified by its serial number.
2026-03-28 fix: break circular dependency between release and merge_bin
2026-06-24 Update Makefile
    updated to work with MeterLoggerWeb and the web builder

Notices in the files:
parts and their libraries:
SparkFun-Connectors: Licensing: CC v3.0 Share-Alike You are welcome to use this library for commercial purposes.
